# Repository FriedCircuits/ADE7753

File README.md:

ADE7753
=======
The design is my own but the code is not. I will post the link to where I found the code when I find the site.

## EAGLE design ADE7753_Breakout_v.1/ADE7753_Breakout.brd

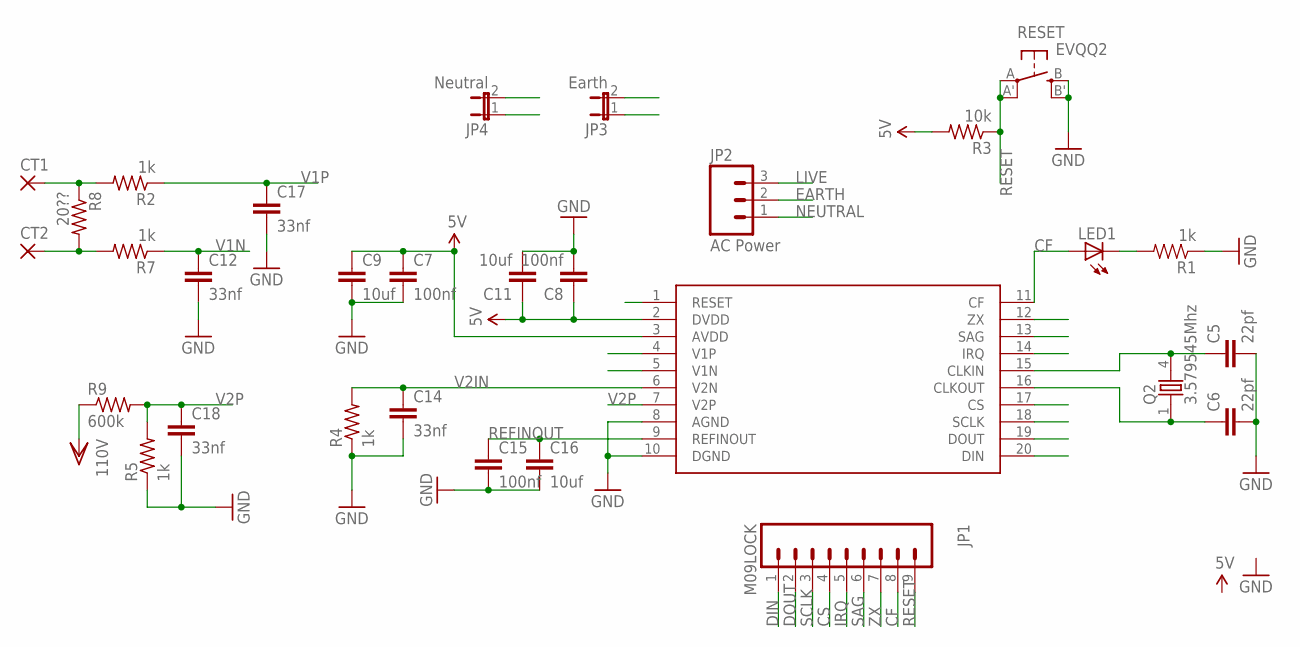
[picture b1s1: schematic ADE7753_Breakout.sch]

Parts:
C5, C6: 22pf; 0805
C7, C8, C15: 100nf; 0805
C9, C11, C16: 10uf; 0805
C12, C14, C17, C18: 33nf; 0805
CT1, CT2: 2,54/1,0
JP1: M09LOCK; 1X09_LOCK
JP2: AC Power; SCREWTERMINAL-3.5MM-3_LOCK.007S
JP3: Earth; 1X02_LOCK
JP4: Neutral; 1X02_LOCK
LED1: LEDCHIP-LED0805; CHIP-LED0805
Q2: 3.579545Mhz; 86SMX
R1: 1k; 0805
R2, R4, R5, R7: 1k; R0805
R3: 10k; R0805
R8: 20??; R0805
R9: 600k; R0805
RESET: EVQQ2; EVQ-Q2
U$1: ADE7753; SSOP20

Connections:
5V: C7.1, C8.1, C9.1, C11.1, R3.2, U$1.2 (DVDD), U$1.3 (AVDD); also elsewhere on the board
CF: JP1.8, LED1.A, U$1.11 (CF); also elsewhere on the board
CLKIN: C5.1, Q2.4 (2), U$1.15 (CLKIN); also elsewhere on the board
CLKOUT: C6.1, Q2.1, U$1.16 (CLKOUT); also elsewhere on the board
CS: JP1.4, U$1.17 (CS); also elsewhere on the board
DIN: JP1.1, U$1.20 (DIN); also elsewhere on the board
DOUT: JP1.2, U$1.19 (DOUT); also elsewhere on the board
EARTH: JP2.2, JP3.2
GND: C5.2, C6.2, C7.2, C8.2, C9.2, C11.2, C12.2, C14.2, C15.2, C16.2, C17.2, C18.2, JP3.1, JP4.1, R1.1, R4.1, R5.1, RESET.B (S), RESET.B' (S1), U$1.8 (AGND), U$1.10 (DGND); also elsewhere on the board
IRQ: JP1.5, U$1.14 (IRQ); also elsewhere on the board
LIVE: JP2.3, R9.1
unnamed: CT1.1, R2.2, R8.1
unnamed: CT2.1, R7.2, R8.2
unnamed: LED1.C, R1.2
NEUTRAL: JP2.1, JP4.2
REFINOUT: C15.1, C16.1, U$1.9 (REFINOUT); also elsewhere on the board
RESET: JP1.9, R3.1, RESET.A, RESET.A' (P1), U$1.1 (RESET); also elsewhere on the board
SAG: JP1.6, U$1.13 (SAG); also elsewhere on the board
SCLK: JP1.3, U$1.18 (SCLK); also elsewhere on the board
V1N: C12.1, R7.1, U$1.5 (V1N); also elsewhere on the board
V1P: C17.1, R2.1, U$1.4 (V1P); also elsewhere on the board
V2IN: C14.1, R4.2, U$1.6 (V2N); also elsewhere on the board
V2P: C18.1, R5.2, R9.2, U$1.7 (V2P); also elsewhere on the board
ZX: JP1.7, U$1.12 (ZX); also elsewhere on the board

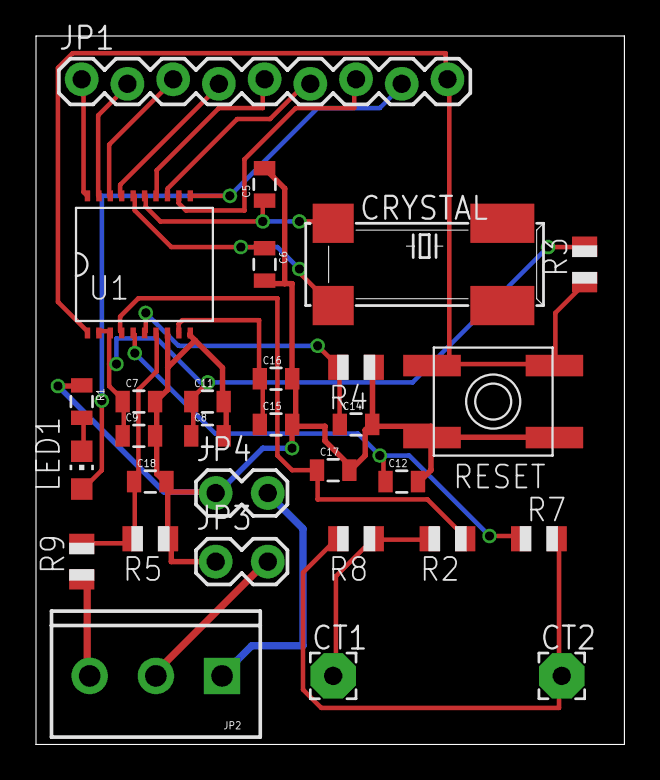
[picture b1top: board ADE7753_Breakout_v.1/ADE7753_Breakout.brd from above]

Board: 2 copper layers, 32.7 x 39.4 mm, 30 parts (0 on the bottom side), 24 nets.

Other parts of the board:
CRYSTAL: 3.579545Mhz; 86SMX
U1: ADE7753; SSOP20

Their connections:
5V: U1.2, U1.3; also elsewhere on the board
CF: U1.11; also elsewhere on the board
CLKIN: CRYSTAL.4, U1.15; also elsewhere on the board
CLKOUT: CRYSTAL.1, U1.16; also elsewhere on the board
CS: U1.17; also elsewhere on the board
DIN: U1.20; also elsewhere on the board
DOUT: U1.19; also elsewhere on the board
GND: U1.8, U1.10; also elsewhere on the board
IRQ: U1.14; also elsewhere on the board
REFINOUT: U1.9; also elsewhere on the board
RESET: U1.1; also elsewhere on the board
SAG: U1.13; also elsewhere on the board
SCLK: U1.18; also elsewhere on the board
V1N: U1.5; also elsewhere on the board
V1P: U1.4; also elsewhere on the board
V2IN: U1.6; also elsewhere on the board
V2P: U1.7; also elsewhere on the board
ZX: U1.12; also elsewhere on the board

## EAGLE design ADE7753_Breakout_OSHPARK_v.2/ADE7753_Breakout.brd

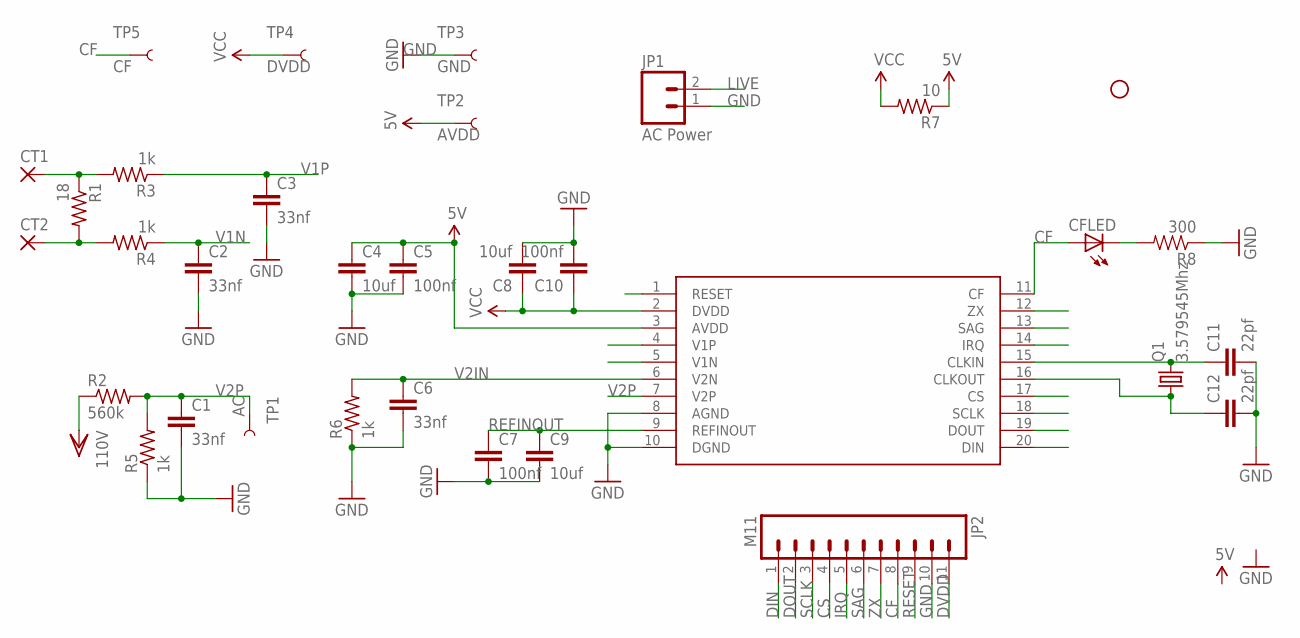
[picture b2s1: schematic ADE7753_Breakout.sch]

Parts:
C1, C2, C3, C6: 33nf; 0805
C4, C8, C9: 10uf; 0805
C5, C7, C10: 100nf; 0805
C11, C12: 22pf; 0805
CFLED: LEDCHIP-LED0805; CHIP-LED0805
CT1, CT2: 2,54/1,0
JP1: AC Power; SCREWTERMINAL-5MM-2
JP2: M11; 1X11_LOCK
JP3: STAND-OFF
Q1: 3.579545Mhz; HC49UP
R1: 18; R0805
R2: 560k; R0805
R3, R4, R5, R6: 1k; R0805
R7: 10; R0805
R8: 300; 0805
TP1: AC; PAD.03X.03
TP2: AVDD; PAD.03X.03
TP3: GND; PAD.03X.03
TP4: DVDD; PAD.03X.03
TP5: CF; PAD.03X.03
U1: ADE7753; SSOP20

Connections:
AVDD: C4.1, C5.1, R7.1, TP2.P$1, U1.3 (AVDD)
CF: CFLED.A, JP2.8, TP5.P$1, U1.11 (CF)
CLKIN: C11.1, Q1.2, U1.15 (CLKIN)
CLKOUT: C12.1, Q1.1, U1.16 (CLKOUT)
CS: JP2.4, U1.17 (CS)
DIN: JP2.1, U1.20 (DIN)
DOUT: JP2.2, U1.19 (DOUT)
DVDD: C8.1, C10.1, JP2.11, R7.2, TP4.P$1, U1.2 (DVDD)
GND: C1.2, C2.2, C3.2, C4.2, C5.2, C6.2, C7.2, C8.2, C9.2, C10.2, C11.2, C12.2, JP1.1, JP2.10, R5.1, R6.1, R8.1, TP3.P$1, U1.8 (AGND), U1.10 (DGND)
IRQ: JP2.5, U1.14 (IRQ)
LIVE: JP1.2, R2.1
unnamed: CT1.1, R1.1, R3.2
unnamed: CT2.1, R1.2, R4.2
unnamed: CFLED.C, R8.2
REFINOUT: C7.1, C9.1, U1.9 (REFINOUT)
RESET: JP2.9, U1.1 (RESET)
SAG: JP2.6, U1.13 (SAG)
SCLK: JP2.3, U1.18 (SCLK)
V1N: C2.1, R4.1, U1.5 (V1N)
V1P: C3.1, R3.1, U1.4 (V1P)
V2IN: C6.1, R6.2, U1.6 (V2N)
V2P: C1.1, R2.2, R5.2, TP1.P$1, U1.7 (V2P)
ZX: JP2.7, U1.12 (ZX)

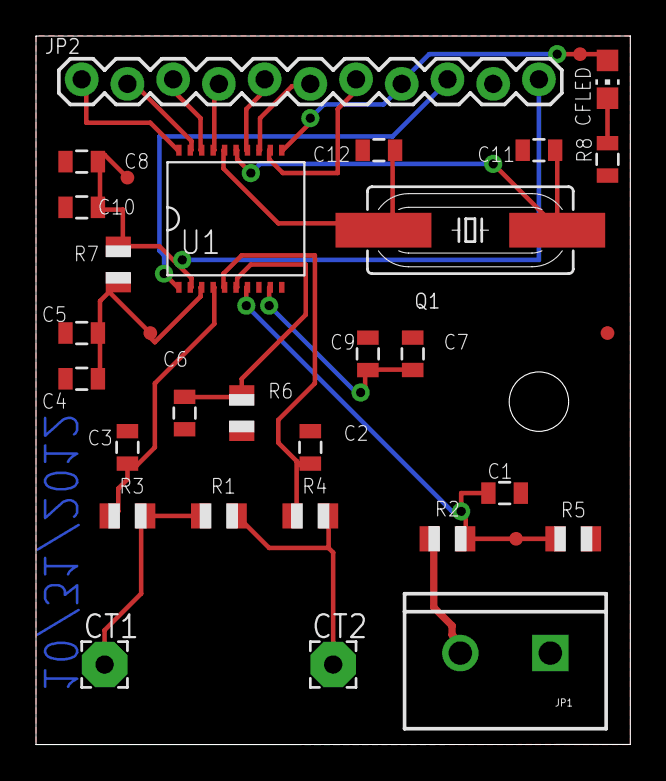
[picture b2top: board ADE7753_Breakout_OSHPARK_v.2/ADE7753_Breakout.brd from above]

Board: 2 copper layers, 33.0 x 39.4 mm, 33 parts (0 on the bottom side), 23 nets.

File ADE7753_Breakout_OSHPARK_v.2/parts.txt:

Partlist

Exported from ADE7753_Breakout.sch at 11/1/2012 12:15:35 AM

EAGLE Version 6.3.0 Copyright (c) 1988-2012 CadSoft

Assembly variant: 

Part     Value          Device          Package             Library             Sheet

C1       33nf           CAP0805         0805                SparkFun-Passives   1
C2       33nf           CAP0805         0805                SparkFun-Passives   1
C3       33nf           CAP0805         0805                SparkFun-Passives   1
C4       10uf           CAP0805         0805                SparkFun-Passives   1
C5       100nf          CAP0805         0805                SparkFun-Passives   1
C6       33nf           CAP0805         0805                SparkFun-Passives   1
C7       100nf          CAP0805         0805                SparkFun-Passives   1
C8       10uf           CAP0805         0805                SparkFun-Passives   1
C9       10uf           CAP0805         0805                SparkFun-Passives   1
C10      100nf          CAP0805         0805                SparkFun-Passives   1
C11      22pf           CAP0805         0805                SparkFun-Passives   1
C12      22pf           CAP0805         0805                SparkFun-Passives   1
CFLED                   LEDCHIP-LED0805 CHIP-LED0805        led                 1
CT1                     2,54/1,0        2,54/1,0            wirepad             1
CT2                     2,54/1,0        2,54/1,0            wirepad             1
JP1      AC Power       M025MM          SCREWTERMINAL-5MM-2 SparkFun-Connectors 1
JP2      M11            M11LOCK         1X11_LOCK           SparkFun-Connectors 1
Q1       3.579545Mhz    CRYSTALSMD      HC49UP              SparkFun-FreqCtrl   1
R1       18             R-US_R0805      R0805               adafruit            1
R2       560k           R-US_R0805      R0805               adafruit            1
R3       1k             R-US_R0805      R0805               adafruit            1
R4       1k             R-US_R0805      R0805               adafruit            1
R5       1k             R-US_R0805      R0805               adafruit            1
R6       1k             R-US_R0805      R0805               adafruit            1
R7       10             R-US_R0805      R0805               adafruit            1
R8       300            RESISTOR        0805                SparkFun            1
TP1      AC             TEST-POINT3     PAD.03X.03          SparkFun-Passives   1
TP2      AVDD           TEST-POINT3     PAD.03X.03          SparkFun-Passives   1
TP3      GND            TEST-POINT3     PAD.03X.03          SparkFun-Passives   1
TP4      DVDD           TEST-POINT3     PAD.03X.03          SparkFun-Passives   1
TP5      CF             TEST-POINT3     PAD.03X.03          SparkFun-Passives   1
U1       ADE7753        ADE7753         SSOP20              ade7735             1

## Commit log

2013-08-08 Renamed folders
2013-08-08 Added PNG
2014-03-30 Rename ADE7752/ADE7753.ino to ADE7753/ADE7753.ino

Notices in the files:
parts and their libraries:
SparkFun-Passives: Licensing: CC v3.0 Share-Alike You are welcome to use this library for commercial purposes.
